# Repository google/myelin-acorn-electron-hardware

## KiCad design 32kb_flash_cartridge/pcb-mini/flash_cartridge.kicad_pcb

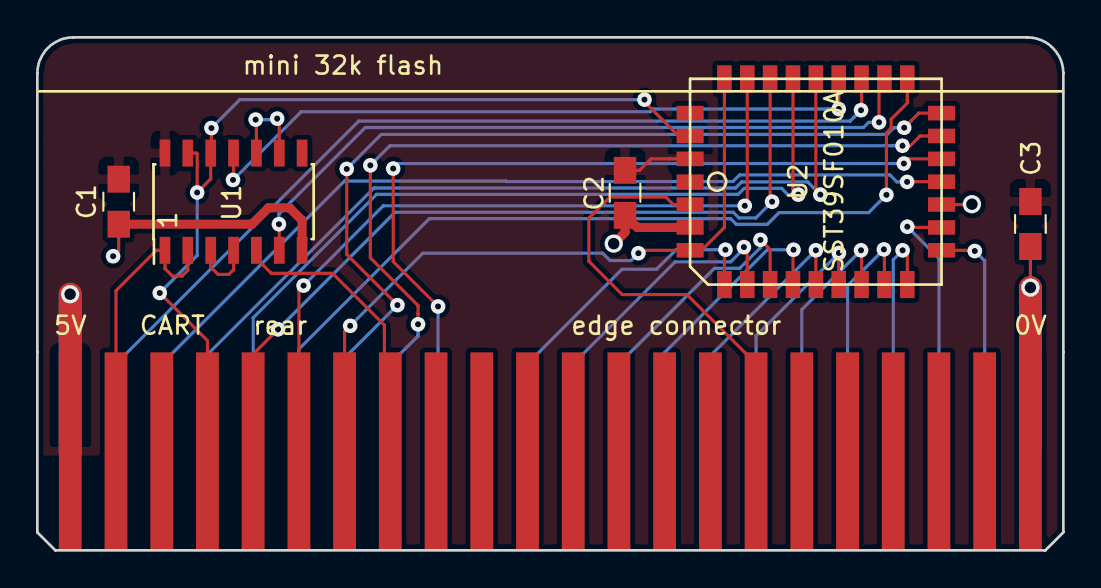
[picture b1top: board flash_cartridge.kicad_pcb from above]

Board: 2 copper layers, 57.0 x 28.5 mm, 6 parts (0 on the bottom side), 31 nets.

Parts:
C1, C2: 100n; C_0805_HandSoldering
C3: 10u; C_0805_HandSoldering
CART: edge connector; acorn_electron_cartridge_edge_connector
U1: 74HCT00; SOIC-14_3.9x8.7mm_Pitch1.27mm
U2: SST39SF010A; sst_plcc32_nh

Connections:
5V: C1.1, C2.1, C3.1, CART.A1, CART.B1, U1.14, U2.32
GND: C1.2, C2.2, C3.2, CART.A22, CART.B22, U1.7, U1.9, U1.10, U2.3, U2.16
elk_A0: CART.B18, U2.12
elk_A1: CART.B17, U2.11
elk_A2: CART.B16, U2.10
elk_A3: CART.B15, U2.9
elk_A4: CART.B14, U2.8
elk_A5: CART.B13, U2.7
elk_A6: CART.B12, U2.6
elk_A7: CART.B11, U2.5
elk_A8: CART.A5, U2.27
elk_A9: CART.B5, U2.26
elk_A10: CART.B2, U2.23
elk_A11: CART.B4, U2.25
elk_A12: CART.A7, U2.4, U2.29
elk_A13: CART.A6, U2.28
elk_D0: CART.B19, U2.13
elk_D1: CART.B21, U2.14
elk_D2: CART.B20, U2.15
elk_D3: CART.B3, U2.17
elk_D4: CART.B9, U2.18
elk_D5: CART.B8, U2.19
elk_D6: CART.B7, U2.20
elk_D7: CART.B6, U2.21
elk_PHI0: CART.A8, U1.5
elk_ROMQA: CART.A16, U2.2
elk_RnW: CART.A4, U1.12, U1.13, U2.31
elk_nOE: CART.A2, U1.1, U1.2
flash_nCE: U1.6, U2.22
flash_nOE: U1.11, U2.24
not_elk_nOE: U1.3, U1.4

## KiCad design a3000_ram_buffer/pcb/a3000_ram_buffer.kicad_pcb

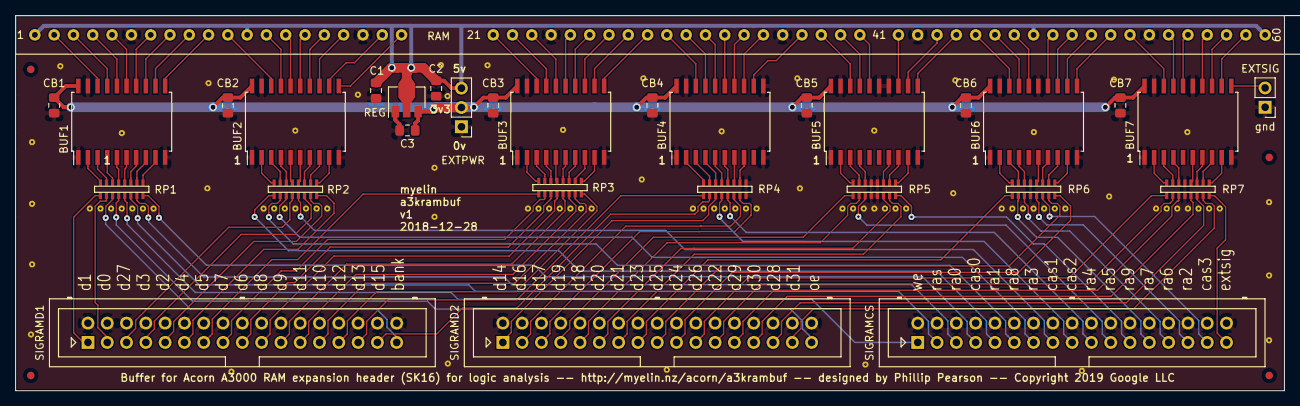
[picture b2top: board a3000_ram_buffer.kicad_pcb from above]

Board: 2 copper layers, 167.0 x 49.4 mm, 78 parts (0 on the bottom side), 156 nets.

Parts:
BUF1, BUF2, BUF3, BUF4, BUF5, BUF6, BUF7: 74LVC245; SOIC-20W_7.5x12.8mm_P1.27mm
C1: 10u; C_0805_2012Metric_Pad1.15x1.40mm_HandSolder
C2, C3: 1u; C_0805_2012Metric_Pad1.15x1.40mm_HandSolder
CB1, CB2, CB3, CB4, CB5, CB6, CB7: 100n; C_0805_2012Metric_Pad1.15x1.40mm_HandSolder
EXTPWR: ext pwr; PinHeader_1x03_P2.54mm_Vertical
EXTSIG: ext signal; PinHeader_1x02_P2.54mm_Vertical
FID1, FID2, FID3, FID4: FIDUCIAL; Fiducial_1mm_Dia_2mm_Outer
RAM: Extension socket to connect to RAM header on A300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; a3000_ram_header
REG: MCP1700T-3302E/MB; SOT-89-3
RP1, RP2, RP3, RP4, RP5, RP6, RP7: resistor pack; bourns_cat16_j8_resistor_array
SIGRAMCS: signal header RAMCS; Multicomp_MC9A12-3434_2x17_P2.54mm_Vertical
SIGRAMD1: signal header RAMD1; Multicomp_MC9A12-3434_2x17_P2.54mm_Vertical
SIGRAMD2: signal header RAMD2; Multicomp_MC9A12-3434_2x17_P2.54mm_Vertical
STAPLE1, STAPLE2, STAPLE3, STAPLE4, STAPLE5, STAPLE6, STAPLE7: via array; via_array_1x7_55mil
staple_single1, staple_single2, staple_single3, staple_single4, staple_single5, staple_single6, staple_single7, staple_single8, staple_single9, staple_single10, staple_single11, staple_single12, staple_single13, staple_single14, staple_single15, staple_single16, staple_single17, staple_single18, staple_single19, staple_single20, staple_single21, staple_single22, staple_single23, staple_single24, staple_single25, staple_single26, staple_single27, staple_single28, staple_single29, staple_single30, staple_single31, staple_single32, staple_single33, staple_single34, staple_single35, staple_single36: via_single

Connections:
3V3: BUF1.20, BUF2.20, BUF3.20, BUF4.20, BUF5.20, BUF6.20, BUF7.20, C3.1, CB1.2, CB2.2, CB3.2, CB4.2, CB5.2, CB6.2, CB7.2, EXTPWR.2, REG.3
5V: C1.2, C2.2, EXTPWR.3, RAM.1, RAM.12, RAM.48, RAM.60, REG.2
GND: BUF1.1, BUF1.10, BUF1.19, BUF2.1, BUF2.10, BUF2.19, BUF3.1, BUF3.10, BUF3.19, BUF4.1, BUF4.10, BUF4.11, BUF4.19, BUF5.1, BUF5.10, BUF5.14, BUF5.15, BUF5.19, BUF6.1, BUF6.10, BUF6.15, BUF6.19, BUF7.1, BUF7.10, BUF7.15, BUF7.19, C1.1, C2.1, C3.2, CB1.1, CB2.1, CB3.1, CB4.1, CB5.1, CB6.1, CB7.1, EXTPWR.1, EXTSIG.1, RAM.6, RAM.18, RAM.24, RAM.36, RAM.42, RAM.54, REG.1, RP4.8A, RP4.8B, RP5.4A, RP5.4B, RP5.5A, RP5.5B, RP6.4A, RP6.4B, RP7.4A, RP7.4B, SIGRAMCS.2, SIGRAMCS.4, SIGRAMCS.6, SIGRAMCS.8, SIGRAMCS.10, SIGRAMCS.12, SIGRAMCS.14, SIGRAMCS.16, SIGRAMCS.18, SIGRAMCS.20, SIGRAMCS.22, SIGRAMCS.24, SIGRAMCS.26, SIGRAMCS.28, SIGRAMCS.30, SIGRAMCS.32, SIGRAMCS.34, SIGRAMD1.2, SIGRAMD1.4, SIGRAMD1.6, SIGRAMD1.8, SIGRAMD1.10, SIGRAMD1.12, SIGRAMD1.14, SIGRAMD1.16, SIGRAMD1.18, SIGRAMD1.20, SIGRAMD1.22, SIGRAMD1.24, SIGRAMD1.26, SIGRAMD1.28, SIGRAMD1.30, SIGRAMD1.32, SIGRAMD1.34, SIGRAMD2.2, SIGRAMD2.4, SIGRAMD2.6, SIGRAMD2.8, SIGRAMD2.10, SIGRAMD2.12, SIGRAMD2.14, SIGRAMD2.16, SIGRAMD2.18, SIGRAMD2.20, SIGRAMD2.22, SIGRAMD2.24, SIGRAMD2.26, SIGRAMD2.28, SIGRAMD2.30, SIGRAMD2.32, SIGRAMD2.34, STAPLE1.1, STAPLE1.2, STAPLE1.3, STAPLE1.4, STAPLE1.5, STAPLE1.6, STAPLE1.7, STAPLE2.1, STAPLE2.2, STAPLE2.3, STAPLE2.4, STAPLE2.5, STAPLE2.6, STAPLE2.7, STAPLE3.1, STAPLE3.2, STAPLE3.3, STAPLE3.4, STAPLE3.5, STAPLE3.6, STAPLE3.7, STAPLE4.1, STAPLE4.2, STAPLE4.3, STAPLE4.4, STAPLE4.5, STAPLE4.6, STAPLE4.7, STAPLE5.1, STAPLE5.2, STAPLE5.3, STAPLE5.4, STAPLE5.5, STAPLE5.6, STAPLE5.7, STAPLE6.1, STAPLE6.2, STAPLE6.3, STAPLE6.4, STAPLE6.5, STAPLE6.6, STAPLE6.7, STAPLE7.1, STAPLE7.2, STAPLE7.3, STAPLE7.4, STAPLE7.5, STAPLE7.6, STAPLE7.7, staple_single1.1, staple_single2.1, staple_single3.1, staple_single4.1, staple_single5.1, staple_single6.1, staple_single7.1, staple_single8.1, staple_single9.1, staple_single10.1, staple_single11.1, staple_single12.1, staple_single13.1, staple_single14.1, staple_single15.1, staple_single16.1, staple_single17.1, staple_single18.1, staple_single19.1, staple_single20.1, staple_single21.1, staple_single22.1, staple_single23.1, staple_single24.1, staple_single25.1, staple_single26.1, staple_single27.1, staple_single28.1, staple_single29.1, staple_single30.1, staple_single31.1, staple_single32.1, staple_single33.1, staple_single34.1, staple_single35.1, staple_single36.1
ext_signal: BUF7.11, EXTSIG.2
ext_signal_buf: BUF7.9, RP7.8B
ext_signal_term: RP7.8A, SIGRAMCS.33
ram_BANK: BUF1.16, RAM.4
ram_BANK_buf: BUF1.4, RP1.3B
ram_BANK_term: RP1.3A, SIGRAMD1.33
ram_D0: BUF1.17, RAM.3
ram_D0_buf: BUF1.3, RP1.2B
ram_D0_term: RP1.2A, SIGRAMD1.3
ram_D1: BUF1.18, RAM.2
ram_D1_buf: BUF1.2, RP1.1B
ram_D1_term: RP1.1A, SIGRAMD1.1
ram_D2: BUF2.12, RAM.19
ram_D2_buf: BUF2.8, RP2.7B
ram_D2_term: RP2.7A, SIGRAMD1.9
ram_D3: BUF2.13, RAM.17
ram_D3_buf: BUF2.7, RP2.6B
ram_D3_term: RP2.6A, SIGRAMD1.7
ram_D4: BUF2.11, RAM.20
ram_D4_buf: BUF2.9, RP2.8B
ram_D4_term: RP2.8A, SIGRAMD1.11
ram_D5: BUF3.18, RAM.21
ram_D5_buf: BUF3.2, RP3.1B
ram_D5_term: RP3.1A, SIGRAMD1.13
ram_D6: BUF3.16, RAM.23
ram_D6_buf: BUF3.4, RP3.3B
ram_D6_term: RP3.3A, SIGRAMD1.17
ram_D7: BUF3.17, RAM.22
ram_D7_buf: BUF3.3, RP3.2B
ram_D7_term: RP3.2A, SIGRAMD1.15
ram_D8: BUF3.15, RAM.25
ram_D8_buf: BUF3.5, RP3.4B
ram_D8_term: RP3.4A, SIGRAMD1.19
ram_D9: BUF3.14, RAM.26
ram_D9_buf: BUF3.6, RP3.5B
ram_D9_term: RP3.5A, SIGRAMD1.21
ram_D10: BUF3.12, RAM.28
ram_D10_buf: BUF3.8, RP3.7B
ram_D10_term: RP3.7A, SIGRAMD1.25
ram_D11: BUF3.13, RAM.27
ram_D11_buf: BUF3.7, RP3.6B
ram_D11_term: RP3.6A, SIGRAMD1.23
ram_D12: BUF3.11, RAM.29
ram_D12_buf: BUF3.9, RP3.8B
ram_D12_term: RP3.8A, SIGRAMD1.27
ram_D13: BUF4.18, RAM.30
ram_D13_buf: BUF4.2, RP4.1B
ram_D13_term: RP4.1A, SIGRAMD1.29
ram_D14: BUF4.16, RAM.32
ram_D14_buf: BUF4.4, RP4.3B
ram_D14_term: RP4.3A, SIGRAMD2.1
ram_D15: BUF4.17, RAM.31
ram_D15_buf: BUF4.3, RP4.2B
ram_D15_term: RP4.2A, SIGRAMD1.31
ram_D16: BUF4.13, RAM.35
ram_D16_buf: BUF4.7, RP4.6B
ram_D16_term: RP4.6A, SIGRAMD2.3
ram_D17: BUF4.12, RAM.37
ram_D17_buf: BUF4.8, RP4.7B
ram_D17_term: RP4.7A, SIGRAMD2.5
ram_D18: BUF5.17, RAM.39
ram_D18_buf: BUF5.3, RP5.2B
ram_D18_term: RP5.2A, SIGRAMD2.9
ram_D19: BUF5.18, RAM.38
ram_D19_buf: BUF5.2, RP5.1B
ram_D19_term: RP5.1A, SIGRAMD2.7
ram_D20: BUF5.13, RAM.41
ram_D20_buf: BUF5.7, RP5.6B
ram_D20_term: RP5.6A, SIGRAMD2.11
ram_D21: BUF5.12, RAM.43
ram_D21_buf: BUF5.8, RP5.7B
ram_D21_term: RP5.7A, SIGRAMD2.13
ram_D22: BUF7.17, RAM.55
ram_D22_buf: BUF7.3, RP7.2B
ram_D22_term: RP7.2A, SIGRAMD2.23
ram_D23: BUF6.18, RAM.45
ram_D23_buf: BUF6.2, RP6.1B
ram_D23_term: RP6.1A, SIGRAMD2.15
ram_D24: BUF6.11, RAM.52
ram_D24_buf: BUF6.9, RP6.8B
ram_D24_term: RP6.8A, SIGRAMD2.19
ram_D25: BUF6.12, RAM.51
ram_D25_buf: BUF6.8, RP6.7B
ram_D25_term: RP6.7A, SIGRAMD2.17
ram_D26: BUF7.18, RAM.53
ram_D26_buf: BUF7.2, RP7.1B
ram_D26_term: RP7.1A, SIGRAMD2.21
ram_D27: BUF2.15, RAM.15
ram_D27_buf: BUF2.5, RP2.4B
ram_D27_term: RP2.4A, SIGRAMD1.5
ram_D28: BUF7.13, RAM.58
ram_D28_buf: BUF7.7, RP7.6B
ram_D28_term: RP7.6A, SIGRAMD2.29
ram_D29: BUF7.16, RAM.56
ram_D29_buf: BUF7.4, RP7.3B
ram_D29_term: RP7.3A, SIGRAMD2.25
ram_D30: BUF7.14, RAM.57
ram_D30_buf: BUF7.6, RP7.5B
ram_D30_term: RP7.5A, SIGRAMD2.27
ram_D31: BUF7.12, RAM.59
ram_D31_buf: BUF7.8, RP7.7B
ram_D31_term: RP7.7A, SIGRAMD2.31
ram_RA0: BUF1.12, RAM.9
ram_RA0_buf: BUF1.8, RP1.7B
ram_RA0_term: RP1.7A, SIGRAMCS.5
ram_RA1: BUF2.18, RAM.11
ram_RA1_buf: BUF2.2, RP2.1B
ram_RA1_term: RP2.1A, SIGRAMCS.9
ram_RA2: BUF6.14, RAM.49
ram_RA2_buf: BUF6.6, RP6.5B
ram_RA2_term: RP6.5A, SIGRAMCS.29
ram_RA3: BUF2.16, RAM.14
ram_RA3_buf: BUF2.4, RP2.3B
ram_RA3_term: RP2.3A, SIGRAMCS.13
ram_RA4: BUF4.14, RAM.34
ram_RA4_buf: BUF4.6, RP4.5B
ram_RA4_term: RP4.5A, SIGRAMCS.19
ram_RA5: BUF5.16, RAM.40
ram_RA5_buf: BUF5.4, RP5.3B
ram_RA5_term: RP5.3A, SIGRAMCS.21
ram_RA6: BUF6.16, RAM.47
ram_RA6_buf: BUF6.4, RP6.3B
ram_RA6_term: RP6.3A, SIGRAMCS.27
ram_RA7: BUF6.17, RAM.46
ram_RA7_buf: BUF6.3, RP6.2B
ram_RA7_term: RP6.2A, SIGRAMCS.25
ram_RA8: BUF2.17, RAM.13
ram_RA8_buf: BUF2.3, RP2.2B
ram_RA8_term: RP2.2A, SIGRAMCS.11
ram_RA9: BUF5.11, RAM.44
ram_RA9_buf: BUF5.9, RP5.8B
ram_RA9_term: RP5.8A, SIGRAMCS.23
ram_nCAS0: BUF1.11, RAM.10
ram_nCAS0_buf: BUF1.9, RP1.8B
ram_nCAS0_term: RP1.8A, SIGRAMCS.7
ram_nCAS1: BUF2.14, RAM.16
ram_nCAS1_buf: BUF2.6, RP2.5B
ram_nCAS1_term: RP2.5A, SIGRAMCS.15
ram_nCAS2: BUF4.15, RAM.33
ram_nCAS2_buf: BUF4.5, RP4.4B
ram_nCAS2_term: RP4.4A, SIGRAMCS.17
ram_nCAS3: BUF6.13, RAM.50
ram_nCAS3_buf: BUF6.7, RP6.6B
ram_nCAS3_term: RP6.6A, SIGRAMCS.31
ram_nOE2: BUF1.15, RAM.5
ram_nOE2_buf: BUF1.5, RP1.4B
ram_nOE2_term: RP1.4A, SIGRAMD2.33
ram_nRAS: BUF1.13, RAM.8
ram_nRAS_buf: BUF1.7, RP1.6B
ram_nRAS_term: RP1.6A, SIGRAMCS.3
ram_nWR2: BUF1.14, RAM.7
ram_nWR2_buf: BUF1.6, RP1.5B
ram_nWR2_term: RP1.5A, SIGRAMCS.1

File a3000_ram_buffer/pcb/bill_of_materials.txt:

Identifier	Value	Description	KiCad package
BUF1	74LVC245		Package_SO:SOIC-20W_7.5x12.8mm_P1.27mm
BUF2	74LVC245		Package_SO:SOIC-20W_7.5x12.8mm_P1.27mm
BUF3	74LVC245		Package_SO:SOIC-20W_7.5x12.8mm_P1.27mm
BUF4	74LVC245		Package_SO:SOIC-20W_7.5x12.8mm_P1.27mm
BUF5	74LVC245		Package_SO:SOIC-20W_7.5x12.8mm_P1.27mm
BUF6	74LVC245		Package_SO:SOIC-20W_7.5x12.8mm_P1.27mm
BUF7	74LVC245		Package_SO:SOIC-20W_7.5x12.8mm_P1.27mm
C1	10u	10u capacitor in 0805 package	Capacitor_SMD:C_0805_2012Metric_Pad1.15x1.40mm_HandSolder
C2	1u	1u capacitor in 0805 package	Capacitor_SMD:C_0805_2012Metric_Pad1.15x1.40mm_HandSolder
C3	1u	1u capacitor in 0805 package	Capacitor_SMD:C_0805_2012Metric_Pad1.15x1.40mm_HandSolder
CB1	100n	100n capacitor in 0805 package	Capacitor_SMD:C_0805_2012Metric_Pad1.15x1.40mm_HandSolder
CB2	100n	100n capacitor in 0805 package	Capacitor_SMD:C_0805_2012Metric_Pad1.15x1.40mm_HandSolder
CB3	100n	100n capacitor in 0805 package	Capacitor_SMD:C_0805_2012Metric_Pad1.15x1.40mm_HandSolder
CB4	100n	100n capacitor in 0805 package	Capacitor_SMD:C_0805_2012Metric_Pad1.15x1.40mm_HandSolder
CB5	100n	100n capacitor in 0805 package	Capacitor_SMD:C_0805_2012Metric_Pad1.15x1.40mm_HandSolder
CB6	100n	100n capacitor in 0805 package	Capacitor_SMD:C_0805_2012Metric_Pad1.15x1.40mm_HandSolder
CB7	100n	100n capacitor in 0805 package	Capacitor_SMD:C_0805_2012Metric_Pad1.15x1.40mm_HandSolder
EXTPWR	ext pwr	1x3 0.1 inch male header	Connector_PinHeader_2.54mm:PinHeader_1x03_P2.54mm_Vertical
EXTSIG	ext signal	1x2 0.1 inch male header	Connector_PinHeader_2.54mm:PinHeader_1x02_P2.54mm_Vertical
FID1	FIDUCIAL		Fiducial:Fiducial_1mm_Dia_2mm_Outer
FID2	FIDUCIAL		Fiducial:Fiducial_1mm_Dia_2mm_Outer
FID3	FIDUCIAL		Fiducial:Fiducial_1mm_Dia_2mm_Outer
FID4	FIDUCIAL		Fiducial:Fiducial_1mm_Dia_2mm_Outer
RAM	Extension socket to connect to RAM header on A3000 motherboard, and mezzanine RAM board		myelin-kicad:a3000_ram_header
REG	MCP1700T-3302E/MB	3.3V LDO regulator, e.g. Digikey MCP1700T3302EMBCT-ND.  Search for the exact part number because there are many variants.	Package_TO_SOT_SMD:SOT-89-3
RP1	resistor pack	8 x 68R	myelin-kicad:bourns_cat16_j8_resistor_array
RP2	resistor pack	8 x 68R	myelin-kicad:bourns_cat16_j8_resistor_array
RP3	resistor pack	8 x 68R	myelin-kicad:bourns_cat16_j8_resistor_array
RP4	resistor pack	8 x 68R	myelin-kicad:bourns_cat16_j8_resistor_array
RP5	resistor pack	8 x 68R	myelin-kicad:bourns_cat16_j8_resistor_array
RP6	resistor pack	8 x 68R	myelin-kicad:bourns_cat16_j8_resistor_array
RP7	resistor pack	8 x 68R	myelin-kicad:bourns_cat16_j8_resistor_array
SIGRAMCS	signal header RAMCS	2x17 0.1 inch male header	Connector_Multicomp:Multicomp_MC9A12-3434_2x17_P2.54mm_Vertical
SIGRAMD1	signal header RAMD1	2x17 0.1 inch male header	Connector_Multicomp:Multicomp_MC9A12-3434_2x17_P2.54mm_Vertical
SIGRAMD2	signal header RAMD2	2x17 0.1 inch male header	Connector_Multicomp:Multicomp_MC9A12-3434_2x17_P2.54mm_Vertical
STAPLE1	via array		myelin-kicad:via_array_1x7_55mil
STAPLE2	via array		myelin-kicad:via_array_1x7_55mil
STAPLE3	via array		myelin-kicad:via_array_1x7_55mil
STAPLE4	via array		myelin-kicad:via_array_1x7_55mil
STAPLE5	via array		myelin-kicad:via_array_1x7_55mil
STAPLE6	via array		myelin-kicad:via_array_1x7_55mil
STAPLE7	via array		myelin-kicad:via_array_1x7_55mil

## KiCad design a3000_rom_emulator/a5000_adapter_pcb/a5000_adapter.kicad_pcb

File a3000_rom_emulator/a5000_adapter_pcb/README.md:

Adapter board to allow an "arcflash" A3000 ROM emulator to work on an A5000.

Pictures
--------

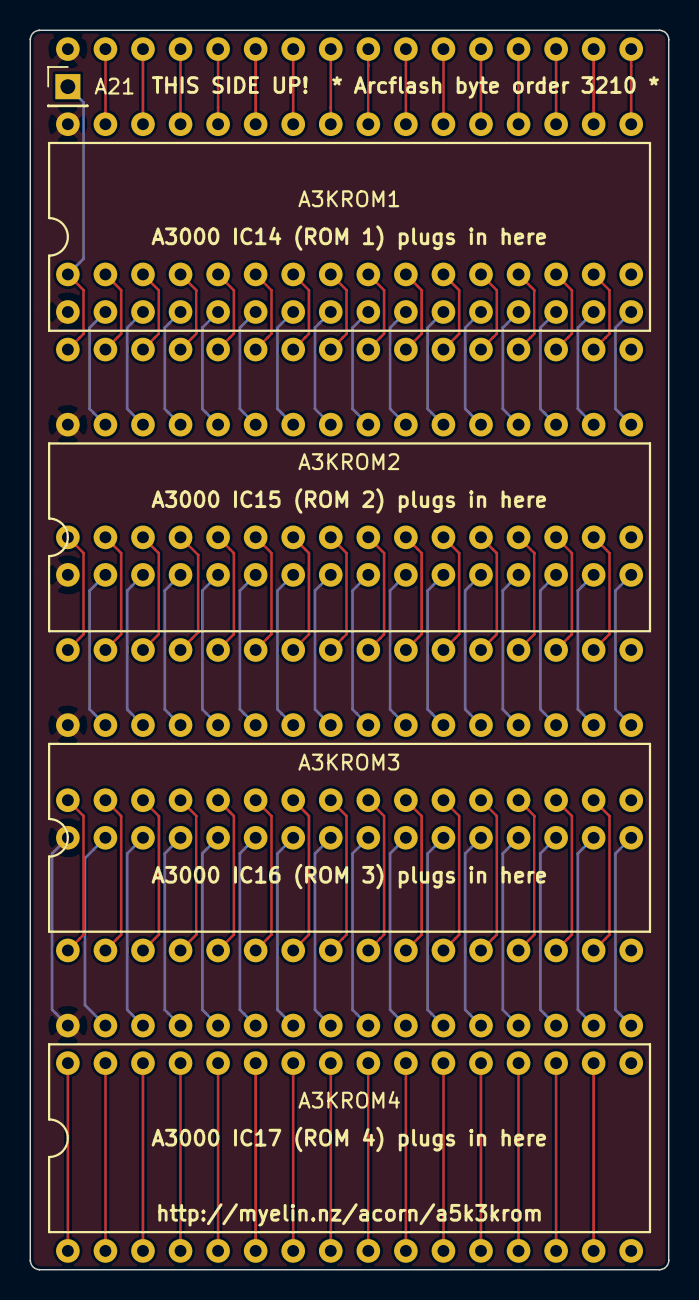
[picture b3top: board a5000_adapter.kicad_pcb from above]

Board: 2 copper layers, 43.2 x 83.8 mm, 9 parts (0 on the bottom side), 122 nets.

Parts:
A3KROM1, A3KROM2, A3KROM3, A3KROM4: ROM header; dip32_rom
A5KROM1, A5KROM2, A5KROM3, A5KROM4: ROM header; dip32_rom_bottom
A21: PinHeader_1x01_P2.54mm_Vertical

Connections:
GND: A3KROM1.16, A3KROM2.16, A3KROM3.16, A3KROM4.16, A5KROM1.16, A5KROM2.16, A5KROM3.16, A5KROM4.16
rom1_pin1: A3KROM1.1, A5KROM1.1, A21.1
rom1_pin2: A3KROM1.2, A5KROM1.2
rom1_pin3: A3KROM1.3, A5KROM1.3
rom1_pin4: A3KROM1.4, A5KROM1.4
rom1_pin5: A3KROM1.5, A5KROM1.5
rom1_pin6: A3KROM1.6, A5KROM1.6
rom1_pin7: A3KROM1.7, A5KROM1.7
rom1_pin8: A3KROM1.8, A5KROM1.8
rom1_pin9: A3KROM1.9, A5KROM1.9
rom1_pin10: A3KROM1.10, A5KROM1.10
rom1_pin11: A3KROM1.11, A5KROM1.11
rom1_pin12: A3KROM1.12, A5KROM1.12
rom1_pin13: A3KROM1.13, A5KROM1.13
rom1_pin14: A3KROM1.14, A5KROM1.14
rom1_pin15: A3KROM1.15, A5KROM1.15
rom1_pin17: A3KROM1.17, A5KROM1.17
rom1_pin18: A3KROM1.18, A5KROM1.18
rom1_pin19: A3KROM1.19, A5KROM1.19
rom1_pin20: A3KROM1.20, A5KROM1.20
rom1_pin21: A3KROM1.21, A5KROM1.21
rom1_pin22: A3KROM1.22, A5KROM1.22
rom1_pin23: A3KROM1.23, A5KROM1.23
rom1_pin24: A3KROM1.24, A5KROM1.24
rom1_pin25: A3KROM1.25, A5KROM1.25
rom1_pin26: A3KROM1.26, A5KROM1.26
rom1_pin27: A3KROM1.27, A5KROM1.27
rom1_pin28: A3KROM1.28, A5KROM1.28
rom1_pin29: A3KROM1.29, A5KROM1.29
rom1_pin30: A3KROM1.30, A5KROM1.30
rom1_pin31: A3KROM1.31, A5KROM1.31
rom2_pin1: A3KROM2.1, A5KROM2.1
rom2_pin2: A3KROM2.2, A5KROM2.2
rom2_pin3: A3KROM2.3, A5KROM2.3
rom2_pin4: A3KROM2.4, A5KROM2.4
rom2_pin5: A3KROM2.5, A5KROM2.5
rom2_pin6: A3KROM2.6, A5KROM2.6
rom2_pin7: A3KROM2.7, A5KROM2.7
rom2_pin8: A3KROM2.8, A5KROM2.8
rom2_pin9: A3KROM2.9, A5KROM2.9
rom2_pin10: A3KROM2.10, A5KROM2.10
rom2_pin11: A3KROM2.11, A5KROM2.11
rom2_pin12: A3KROM2.12, A5KROM2.12
rom2_pin13: A3KROM2.13, A5KROM2.13
rom2_pin14: A3KROM2.14, A5KROM2.14
rom2_pin15: A3KROM2.15, A5KROM2.15
rom2_pin17: A3KROM2.17, A5KROM2.17
rom2_pin18: A3KROM2.18, A5KROM2.18
rom2_pin19: A3KROM2.19, A5KROM2.19
rom2_pin20: A3KROM2.20, A5KROM2.20
rom2_pin21: A3KROM2.21, A5KROM2.21
rom2_pin22: A3KROM2.22, A5KROM2.22
rom2_pin23: A3KROM2.23, A5KROM2.23
rom2_pin24: A3KROM2.24, A5KROM2.24
rom2_pin25: A3KROM2.25, A5KROM2.25
rom2_pin26: A3KROM2.26, A5KROM2.26
rom2_pin27: A3KROM2.27, A5KROM2.27
rom2_pin28: A3KROM2.28, A5KROM2.28
rom2_pin29: A3KROM2.29, A5KROM2.29
rom2_pin30: A3KROM2.30, A5KROM2.30
rom2_pin31: A3KROM2.31, A5KROM2.31
rom3_pin1: A3KROM3.1, A5KROM3.1
rom3_pin2: A3KROM3.2, A5KROM3.2
rom3_pin3: A3KROM3.3, A5KROM3.3
rom3_pin4: A3KROM3.4, A5KROM3.4
rom3_pin5: A3KROM3.5, A5KROM3.5
rom3_pin6: A3KROM3.6, A5KROM3.6
rom3_pin7: A3KROM3.7, A5KROM3.7
rom3_pin8: A3KROM3.8, A5KROM3.8
rom3_pin9: A3KROM3.9, A5KROM3.9
rom3_pin10: A3KROM3.10, A5KROM3.10
rom3_pin11: A3KROM3.11, A5KROM3.11
rom3_pin12: A3KROM3.12, A5KROM3.12
rom3_pin13: A3KROM3.13, A5KROM3.13
rom3_pin14: A3KROM3.14, A5KROM3.14
rom3_pin15: A3KROM3.15, A5KROM3.15
rom3_pin17: A3KROM3.17, A5KROM3.17
rom3_pin18: A3KROM3.18, A5KROM3.18
rom3_pin19: A3KROM3.19, A5KROM3.19
rom3_pin20: A3KROM3.20, A5KROM3.20
rom3_pin21: A3KROM3.21, A5KROM3.21
rom3_pin22: A3KROM3.22, A5KROM3.22
rom3_pin23: A3KROM3.23, A5KROM3.23
rom3_pin24: A3KROM3.24, A5KROM3.24
rom3_pin25: A3KROM3.25, A5KROM3.25
rom3_pin26: A3KROM3.26, A5KROM3.26
rom3_pin27: A3KROM3.27, A5KROM3.27
rom3_pin28: A3KROM3.28, A5KROM3.28
rom3_pin29: A3KROM3.29, A5KROM3.29
rom3_pin30: A3KROM3.30, A5KROM3.30
rom3_pin31: A3KROM3.31, A5KROM3.31
rom4_pin1: A3KROM4.1, A5KROM4.1
rom4_pin2: A3KROM4.2, A5KROM4.2
rom4_pin3: A3KROM4.3, A5KROM4.3
rom4_pin4: A3KROM4.4, A5KROM4.4
rom4_pin5: A3KROM4.5, A5KROM4.5
rom4_pin6: A3KROM4.6, A5KROM4.6
rom4_pin7: A3KROM4.7, A5KROM4.7
rom4_pin8: A3KROM4.8, A5KROM4.8
rom4_pin9: A3KROM4.9, A5KROM4.9
rom4_pin10: A3KROM4.10, A5KROM4.10
rom4_pin11: A3KROM4.11, A5KROM4.11
rom4_pin12: A3KROM4.12, A5KROM4.12
rom4_pin13: A3KROM4.13, A5KROM4.13
rom4_pin14: A3KROM4.14, A5KROM4.14
rom4_pin15: A3KROM4.15, A5KROM4.15
rom4_pin17: A3KROM4.17, A5KROM4.17
rom4_pin18: A3KROM4.18, A5KROM4.18
rom4_pin19: A3KROM4.19, A5KROM4.19
rom4_pin20: A3KROM4.20, A5KROM4.20
rom4_pin21: A3KROM4.21, A5KROM4.21
rom4_pin22: A3KROM4.22, A5KROM4.22
rom4_pin23: A3KROM4.23, A5KROM4.23
rom4_pin24: A3KROM4.24, A5KROM4.24
rom4_pin25: A3KROM4.25, A5KROM4.25
rom4_pin26: A3KROM4.26, A5KROM4.26
rom4_pin27: A3KROM4.27, A5KROM4.27
rom4_pin28: A3KROM4.28, A5KROM4.28
rom4_pin29: A3KROM4.29, A5KROM4.29
rom4_pin30: A3KROM4.30, A5KROM4.30
rom4_pin31: A3KROM4.31, A5KROM4.31
rom_5V: A3KROM1.32, A3KROM2.32, A3KROM3.32, A3KROM4.32, A5KROM1.32, A5KROM2.32, A5KROM3.32, A5KROM4.32

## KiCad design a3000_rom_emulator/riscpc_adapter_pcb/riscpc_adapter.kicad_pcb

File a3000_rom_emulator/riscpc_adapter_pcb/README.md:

Adapter board to allow an "arcflash" A3000 ROM emulator to work on a Risc PC.

Pictures
--------

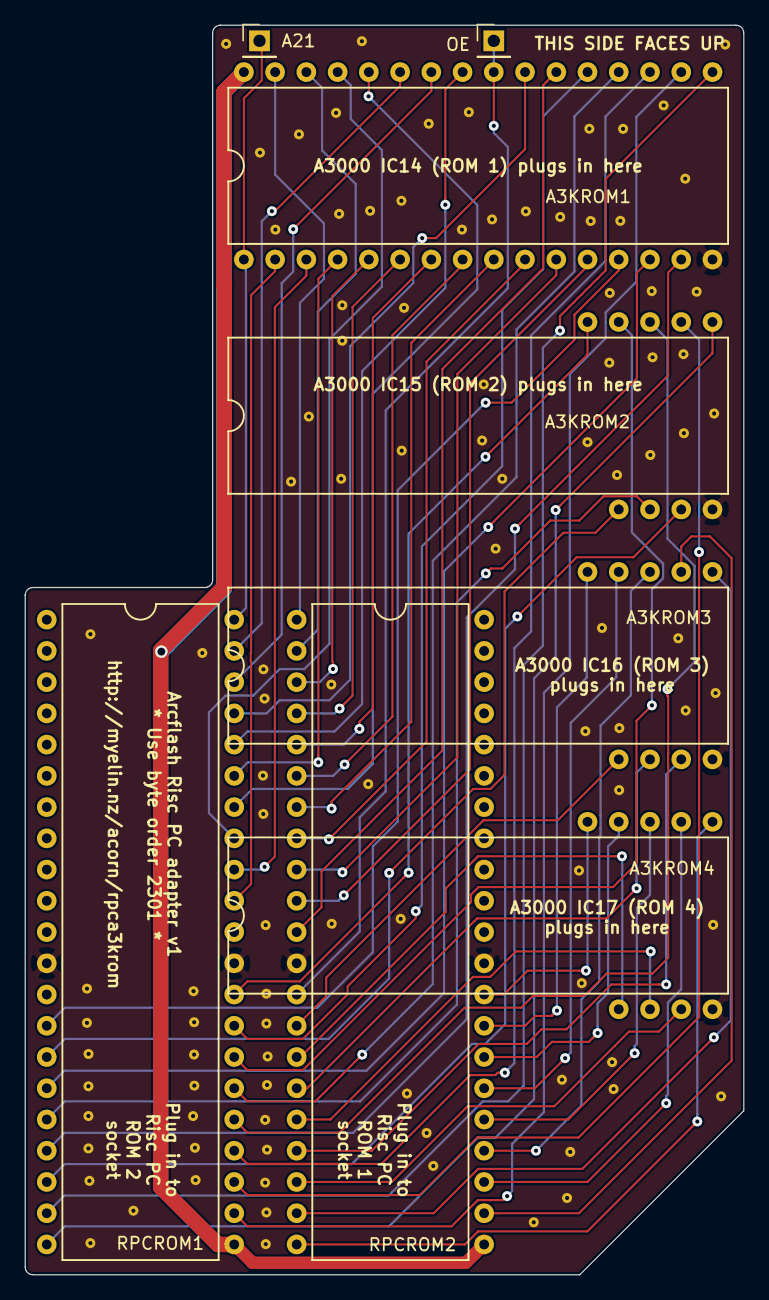
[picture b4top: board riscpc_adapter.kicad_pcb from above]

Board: 2 copper layers, 58.4 x 101.6 mm, 108 parts (0 on the bottom side), 56 nets.

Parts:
A3KROM1: ROM header; dip32_rom
A3KROM2, A3KROM3, A3KROM4: ROM header; dip32_rom_data_only
A21: PinHeader_1x01_P2.54mm_Vertical
OE: PinHeader_1x01_P2.54mm_Vertical
RPCROM1, RPCROM2: ROM header; dip42_rom
staple_single1, staple_single2, staple_single3, staple_single4, staple_single5, staple_single6, staple_single7, staple_single8, staple_single9, staple_single10, staple_single11, staple_single12, staple_single13, staple_single14, staple_single15, staple_single16, staple_single17, staple_single18, staple_single19, staple_single20, staple_single21, staple_single22, staple_single23, staple_single24, staple_single25, staple_single26, staple_single27, staple_single28, staple_single29, staple_single30, staple_single31, staple_single32, staple_single33, staple_single34, staple_single35, staple_single36, staple_single37, staple_single38, staple_single39, staple_single40, staple_single41, staple_single42, staple_single43, staple_single44, staple_single45, staple_single46, staple_single47, staple_single48, staple_single49, staple_single50, staple_single51, staple_single52, staple_single53, staple_single54, staple_single55, staple_single56, staple_single57, staple_single58, staple_single59, staple_single60, staple_single61, staple_single62, staple_single63, staple_single64, staple_single65, staple_single66, staple_single67, staple_single68, staple_single69, staple_single70, staple_single71, staple_single72, staple_single73, staple_single74, staple_single75, staple_single76, staple_single77, staple_single78, staple_single79, staple_single80, staple_single81, staple_single82, staple_single83, staple_single84, staple_single85, staple_single86, staple_single87, staple_single88, staple_single89, staple_single90, staple_single91, staple_single92, staple_single93, staple_single94, staple_single95, staple_single96, staple_single97, staple_single98, staple_single99, staple_single100: via_single

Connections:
5V: A3KROM1.32, RPCROM1.22, RPCROM2.22
A0: A3KROM1.12, RPCROM2.10
A1: A3KROM1.11, RPCROM2.9
A2: A3KROM1.10, RPCROM2.8
A3: A3KROM1.9, RPCROM2.7
A4: A3KROM1.8, RPCROM2.6
A5: A3KROM1.7, RPCROM2.5
A6: A3KROM1.6, RPCROM2.4
A7: A3KROM1.5, RPCROM2.3
A8: A3KROM1.27, RPCROM1.41
A9: A3KROM1.26, RPCROM1.40
A10: A3KROM1.23, RPCROM1.39
A11: A3KROM1.25, RPCROM1.38
A12: A3KROM1.4, RPCROM1.37
A13: A3KROM1.28, RPCROM1.36
A14: A3KROM1.29, RPCROM1.35
A15: A3KROM1.3, RPCROM1.34
A16: A3KROM1.2, RPCROM1.33
A17: A3KROM1.30, RPCROM2.2
A18: A3KROM1.31, RPCROM2.1
A19: A3KROM1.1, A21.1, RPCROM1.42
D0: A3KROM1.13, RPCROM1.14
D1: A3KROM1.14, RPCROM1.16
D2: A3KROM1.15, RPCROM1.18
D3: A3KROM1.17, RPCROM1.20
D4: A3KROM1.18, RPCROM1.23
D5: A3KROM1.19, RPCROM1.25
D6: A3KROM1.20, RPCROM1.27
D7: A3KROM1.21, RPCROM1.29
D8: A3KROM2.13, RPCROM1.15
D9: A3KROM2.14, RPCROM1.17
D10: A3KROM2.15, RPCROM1.19
D11: A3KROM2.17, RPCROM1.21
D12: A3KROM2.18, RPCROM1.24
D13: A3KROM2.19, RPCROM1.26
D14: A3KROM2.20, RPCROM1.28
D15: A3KROM2.21, RPCROM1.30
D16: A3KROM3.13, RPCROM2.14
D17: A3KROM3.14, RPCROM2.16
D18: A3KROM3.15, RPCROM2.18
D19: A3KROM3.17, RPCROM2.20
D20: A3KROM3.18, RPCROM2.23
D21: A3KROM3.19, RPCROM2.25
D22: A3KROM3.20, RPCROM2.27
D23: A3KROM3.21, RPCROM2.29
D24: A3KROM4.13, RPCROM2.15
D25: A3KROM4.14, RPCROM2.17
D26: A3KROM4.15, RPCROM2.19
D27: A3KROM4.17, RPCROM2.21
D28: A3KROM4.18, RPCROM2.24
D29: A3KROM4.19, RPCROM2.26
D30: A3KROM4.20, RPCROM2.28
D31: A3KROM4.21, RPCROM2.30
GND: A3KROM1.16, A3KROM2.16, A3KROM3.16, A3KROM4.16, RPCROM1.12, RPCROM1.31, RPCROM2.12, RPCROM2.31, staple_single1.1, staple_single2.1, staple_single3.1, staple_single4.1, staple_single5.1, staple_single6.1, staple_single7.1, staple_single8.1, staple_single9.1, staple_single10.1, staple_single11.1, staple_single12.1, staple_single13.1, staple_single14.1, staple_single15.1, staple_single16.1, staple_single17.1, staple_single18.1, staple_single19.1, staple_single20.1, staple_single21.1, staple_single22.1, staple_single23.1, staple_single24.1, staple_single25.1, staple_single26.1, staple_single27.1, staple_single28.1, staple_single29.1, staple_single30.1, staple_single31.1, staple_single32.1, staple_single33.1, staple_single34.1, staple_single35.1, staple_single36.1, staple_single37.1, staple_single38.1, staple_single39.1, staple_single40.1, staple_single41.1, staple_single42.1, staple_single43.1, staple_single44.1, staple_single45.1, staple_single46.1, staple_single47.1, staple_single48.1, staple_single49.1, staple_single50.1, staple_single51.1, staple_single52.1, staple_single53.1, staple_single54.1, staple_single55.1, staple_single56.1, staple_single57.1, staple_single58.1, staple_single59.1, staple_single60.1, staple_single61.1, staple_single62.1, staple_single63.1, staple_single64.1, staple_single65.1, staple_single66.1, staple_single67.1, staple_single68.1, staple_single69.1, staple_single70.1, staple_single71.1, staple_single72.1, staple_single73.1, staple_single74.1, staple_single75.1, staple_single76.1, staple_single77.1, staple_single78.1, staple_single79.1, staple_single80.1, staple_single81.1, staple_single82.1, staple_single83.1, staple_single84.1, staple_single85.1, staple_single86.1, staple_single87.1, staple_single88.1, staple_single89.1, staple_single90.1, staple_single91.1, staple_single92.1, staple_single93.1, staple_single94.1, staple_single95.1, staple_single96.1, staple_single97.1, staple_single98.1, staple_single99.1, staple_single100.1
nCS: A3KROM1.22, RPCROM2.11
nOE: A3KROM1.24, OE.1, RPCROM2.13

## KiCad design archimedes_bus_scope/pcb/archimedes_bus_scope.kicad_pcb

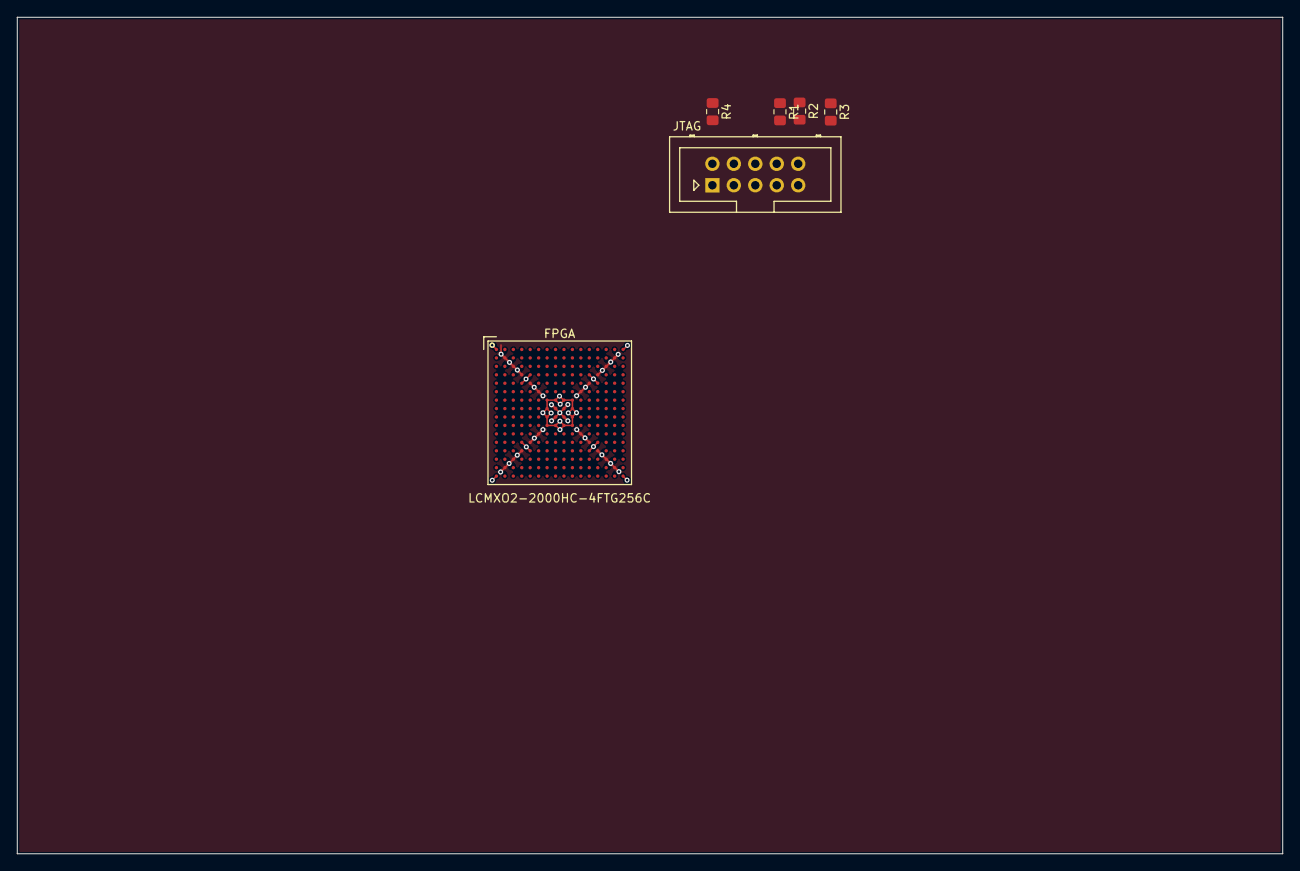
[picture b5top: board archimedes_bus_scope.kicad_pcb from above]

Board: 4 copper layers, 149.9 x 99.1 mm, 6 parts (0 on the bottom side), 9 nets.

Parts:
FPGA: LCMXO2-2000HC-4FTG256C; lattice_ftg256_fbga
JTAG: jtag; Multicomp_MC9A12-1034_2x05_P2.54mm_Vertical
R1, R2, R3: 10k; R_0805_2012Metric_Pad1.15x1.40mm_HandSolder
R4: 4k7; R_0805_2012Metric_Pad1.15x1.40mm_HandSolder

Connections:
3V3: FPGA.A1, FPGA.A16, FPGA.D5, FPGA.D12, FPGA.E4, FPGA.E13, FPGA.G7, FPGA.G8, FPGA.G9, FPGA.G10, FPGA.H7, FPGA.H10, FPGA.J7, FPGA.J10, FPGA.K7, FPGA.K8, FPGA.K9, FPGA.K10, FPGA.M4, FPGA.M13, FPGA.N5, FPGA.N12, FPGA.T1, FPGA.T16, JTAG.6, R1.1, R2.1, R3.1
GND: FPGA.B2, FPGA.B15, FPGA.C3, FPGA.C14, FPGA.D4, FPGA.D13, FPGA.E5, FPGA.E12, FPGA.F6, FPGA.F11, FPGA.H8, FPGA.H9, FPGA.J8, FPGA.J9, FPGA.L6, FPGA.L11, FPGA.M5, FPGA.M12, FPGA.N4, FPGA.N13, FPGA.P3, FPGA.P14, FPGA.R2, FPGA.R15, JTAG.2, JTAG.4, R4.1
fpga_DONE: FPGA.C13, JTAG.9, R3.2
fpga_INITN: FPGA.A13, JTAG.8, R1.2
fpga_PROGRAMN: FPGA.B10, JTAG.10, R2.2
fpga_TCK: FPGA.A7, JTAG.1, R4.2
fpga_TDI: FPGA.A6, JTAG.5
fpga_TDO: FPGA.C6, JTAG.7
fpga_TMS: FPGA.B8, JTAG.3

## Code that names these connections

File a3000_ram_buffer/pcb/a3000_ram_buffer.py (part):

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    pins=[
        # 32 data lines, 8 control lines (bank, oe, wr, ras, 4xcas), four 5V, six GND, 10 address = 60 pins
        Pin( 1, "5V",    "5V"),
        Pin( 2, "Rd1",   "ram_D1"),
        Pin( 3, "Rd0",   "ram_D0"),
        Pin( 4, "Bank",  "ram_BANK"),
        Pin( 5, "Oe2",   "ram_nOE2"),
        Pin( 6, "GND",   "GND"),
        Pin( 7, "Wr2",   "ram_nWR2"),
        Pin( 8, "Ras*",  "ram_nRAS"),
        Pin( 9, "Ra0",   "ram_RA0"),
        Pin(10, "Cas0*", "ram_nCAS0"),
        Pin(11, "Ra1",   "ram_RA1"),
        Pin(12, "5V",    "5V"),
        Pin(13, "Ra8",   "ram_RA8"),
        Pin(14, "Ra3",   "ram_RA3"),
        Pin(15, "Rd27",  "ram_D27"),
        Pin(16, "Cas1*", "ram_nCAS1"),
        Pin(17, "Rd3",   "ram_D3"),
        Pin(18, "GND",   "GND"),
        Pin(19, "Rd2",   "ram_D2"),
        Pin(20, "Rd4",   "ram_D4"),

        Pin(21, "Rd5",   "ram_D5"),
        Pin(22, "Rd7",   "ram_D7"),
        Pin(23, "Rd6",   "ram_D6"),
        Pin(24, "GND",   "GND"),
        Pin(25, "Rd8",   "ram_D8"),
        Pin(26, "Rd9",   "ram_D9"),
        Pin(27, "Rd11",  "ram_D11"),
        Pin(28, "Rd10",  "ram_D10"),
        Pin(29, "Rd12",  "ram_D12"),
        Pin(30, "Rd13",  "ram_D13"),
        Pin(31, "Rd15",  "ram_D15"),
        Pin(32, "Rd14",  "ram_D14"),
        Pin(33, "Cas2*", "ram_nCAS2"),
        Pin(34, "Ra4",   "ram_RA4"),
        Pin(35, "Rd16",  "ram_D16"),
        Pin(36, "GND",   "GND"),
        Pin(37, "Rd17",  "ram_D17"),
        Pin(38, "Rd19",  "ram_D19"),
        Pin(39, "Rd18",  "ram_D18"),
        Pin(40, "Ra5",   "ram_RA5"),
        
        Pin(41, "Rd20",  "ram_D20"),
        Pin(42, "GND",   "GND"),
        Pin(43, "Rd21",  "ram_D21"),
        Pin(44, "Ra9",   "ram_RA9"),
        Pin(45, "Rd23",  "ram_D23"),
        Pin(46, "Ra7",   "ram_RA7"),
        Pin(47, "Ra6",   "ram_RA6"),
        Pin(48, "5V",    "5V"),
        Pin(49, "Ra2",   "ram_RA2"),
        Pin(50, "Cas3*", "ram_nCAS3"),
        Pin(51, "Rd25",  "ram_D25"),
        Pin(52, "Rd24",  "ram_D24"),
        Pin(53, "Rd26",  "ram_D26"),
        Pin(54, "GND",   "GND"),
        Pin(55, "Rd22",  "ram_D22"),
        Pin(56, "Rd29",  "ram_D29"),
        Pin(57, "Rd30",  "ram_D30"),
        Pin(58, "Rd28",  "ram_D28"),
        Pin(59, "Rd31",  "ram_D31"),
        Pin(60, "5V",    "5V"),
    ],
)
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    desc="1x2 0.1 inch male header",
    pins=[
        Pin(1, "", "GND"),
        Pin(2, "", "ext_signal"),
    ],
)

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#             Pin(22, "2B6",  ""),
#             Pin(23, "2B7",  ""),
#             Pin(24, "2DIR", ""),
#             Pin(25, "2nOE", ""),
#             Pin(26, "2A7",  ""),
#             Pin(27, "2A6",  ""),
#             Pin(28, "GND",  "GND"),
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#             Pin(45, "GND",  "GND"),
#             Pin(46, "1A1",  ""),
#             Pin(47, "1A0",  ""),
#             Pin(48, "1nOE", ""),
#         ],
#     ),
# ]
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
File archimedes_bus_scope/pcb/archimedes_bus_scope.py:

#!/usr/bin/python

# Copyright 2018 Google LLC
#
# Licensed under the Apache License, Version 2.0 (the "License");
# you may not use this file except in compliance with the License.
# You may obtain a copy of the License at
#
#     http://www.apache.org/licenses/LICENSE-2.0
#
# Unless required by applicable law or agreed to in writing, software
# distributed under the License is distributed on an "AS IS" BASIS,
# WITHOUT WARRANTIES OR CONDITIONS OF ANY KIND, either express or implied.
# See the License for the specific language governing permissions and
# limitations under the License.

# --------------------
# archimedes_bus_scope
# --------------------

# by Phillip Pearson

# Interface board to allow sampling 128-ish logic channels over USB 3


PROJECT_NAME = "archimedes_bus_scope"


import sys, os
here = os.path.dirname(sys.argv[0])
sys.path.insert(0, os.path.join(here, "../../third_party/myelin-kicad.pretty"))
import myelin_kicad_pcb
Pin = myelin_kicad_pcb.Pin


"""
### FPGA connections: 207 IOs, and a bunch of VCC/GND/etc


### FX3 connections

# to FPGA: 32+12=44 pins
DQ0-31
PCLK # clock from FPGA
CTL0_SLCS# # select fx3
CTL1_SLWR# # write to fx3
CTL2_SLOE# # enable fx3 outputs
CTL3_SLRD# # read from fx3
CTL4_FLAGA
CTL5_FLAGB
CTL6_EPSWITCH
CTL7_PKTEND# # last byte of packet
CTL11_A1 # address
CTL12_A0 # address
CTL15_INT# # interrupt from fx3 to fpga

# to external?
GPIO45
GPIO53_RTS_SCK
GPIO54_CTS_SSN
GPIO55_TX_MISO
GPIO56_RX_MOSI

"""

# TODO think about footprint here.
# kicad's Package_BGA:BGA-256_17.0x17.0mm_Layout16x16_P1.0mm_Ball0.5mm_Pad0.4mm_NSMD
# has 0.4mm balls, which end up as 0.654mm with my 5 mil clearance, so have 0.346mm (13.6 mil)
# between them, i.e. plenty for two 4 mil traces and a 5 mil gap (13 mil).
# My myelin-kicad:cypress_lae064_fbga has 0.45mm balls, so 0.704 with clearance, and only 11.65 mil gap.

fpga = [
    myelin_kicad_pcb.Component(
        footprint="myelin-kicad:lattice_ftg256_fbga",
        identifier="FPGA",
        value="LCMXO2-2000HC-4FTG256C",
        buses=[""],
        pins=[
            # generated by make_machxo2_power_gnd_ball_map.py
            Pin("B2", "GND", "GND"),
            Pin("B15", "GND", "GND"),
            Pin("C3", "GND", "GND"),
            Pin("C14", "GND", "GND"),
            Pin("D4", "GND", "GND"),
            Pin("D13", "GND", "GND"),
            Pin("E5", "GND", "GND"),
            Pin("E12", "GND", "GND"),
            Pin("F6", "GND", "GND"),
            Pin("F11", "GND", "GND"),
            Pin("H8", "GND", "GND"),
            Pin("H9", "GND", "GND"),
            Pin("J8", "GND", "GND"),
            Pin("J9", "GND", "GND"),
            Pin("L6", "GND", "GND"),
            Pin("L11", "GND", "GND"),
            Pin("M5", "GND", "GND"),
            Pin("M12", "GND", "GND"),
            Pin("N4", "GND", "GND"),
            Pin("N13", "GND", "GND"),
            Pin("P3", "GND", "GND"),
            Pin("P14", "GND", "GND"),
            Pin("R2", "GND", "GND"),
            Pin("R15", "GND", "GND"),
            Pin("A1", "VCC", "3V3"),
            Pin("A16", "VCC", "3V3"),
            Pin("G7", "VCC", "3V3"),
            Pin("G10", "VCC", "3V3"),
            Pin("K7", "VCC", "3V3"),
            Pin("K10", "VCC", "3V3"),
            Pin("T1", "VCC", "3V3"),
            Pin("T16", "VCC", "3V3"),
            Pin("D5", "VCCIO0", "3V3"),
            Pin("D12", "VCCIO0", "3V3"),
            Pin("G8", "VCCIO0", "3V3"),
            Pin("G9", "VCCIO0", "3V3"),
            Pin("E13", "VCCIO1", "3V3"),
            Pin("H10", "VCCIO1", "3V3"),
            Pin("J10", "VCCIO1", "3V3"),
            Pin("M13", "VCCIO1", "3V3"),
            Pin("K8", "VCCIO2", "3V3"),
            Pin("K9", "VCCIO2", "3V3"),
            Pin("N5", "VCCIO2", "3V3"),
            Pin("N12", "VCCIO2", "3V3"),
            Pin("M4", "VCCIO3", "3V3"),
            Pin("H7", "VCCIO4", "3V3"),
            Pin("J7", "VCCIO4", "3V3"),
            Pin("E4", "VCCIO5", "3V3"),
            Pin("A2", "NC", "NC"),
        ] + [
            # Reserved during startup -- better leave NC or bring out to FX3
            Pin("A13", "INITN", "fpga_INITN"),
            Pin("B10", "PROGRAMN", "fpga_PROGRAMN"),
            Pin("C13", "DONE", "fpga_DONE"),

            # JTAG
            Pin("A6", "TDI", "fpga_TDI"),
            Pin("A7", "TCK", "fpga_TCK"),
            Pin("B8", "TMS", "fpga_TMS"),
            Pin("C6", "TDO", "fpga_TDO"),
        ] + [
            # User IO
        ],
    )
]

# MachXO2 needs a pullup on INITN to complete configuration, and pullups are also recommended on PROGRAMN and DONE.
# For JTAG, TMS, TDI, TDO have internal weak pullups, and TCK needs a 4k7 pulldown.
fpga_pullups = [
    myelin_kicad_pcb.R0805("10k", "3V3", "fpga_INITN"),
    myelin_kicad_pcb.R0805("10k", "3V3", "fpga_PROGRAMN"),
    myelin_kicad_pcb.R0805("10k", "3V3", "fpga_DONE"),
    myelin_kicad_pcb.R0805("4k7", "GND", "fpga_TCK"),
]

# TODO MachXO2 JTAG header, Lattice format
# See: https://github.com/google/myelin-acorn-electron-hardware/blob/master/notes/pld_programming_and_jtag.md
cpld_jtag = myelin_kicad_pcb.Component(
    footprint="Connector_Multicomp:Multicomp_MC9A12-1034_2x05_P2.54mm_Vertical",
    identifier="JTAG",
    value="jtag",
    desc="2x5 header for JTAG programming.  Use generic 0.1 inch header strip or Digikey ED1543-ND.",
    pins=[
        Pin( 1, "TCK",  "fpga_TCK"), # top left
        Pin( 2, "GND",  "GND"),      # top right
        Pin( 3, "TMS",  "fpga_TMS"),
        Pin( 4, "GND",  "GND"),
        Pin( 5, "TDI",  "fpga_TDI"),
        Pin( 6, "VCC",  "3V3"),
        Pin( 7, "TDO",  "fpga_TDO"),
        Pin( 8, "INIT", "fpga_INITN"),
        Pin( 9, "TRST", "fpga_DONE"),
        Pin(10, "PROG", "fpga_PROGRAMN"),
    ],
)
# I wasn't sure whether to put INIT on pin 8 or not -- uncomment this to make a test point for it
# cpld_INITN_TP = cpld_jtag = myelin_kicad_pcb.Component(
#     footprint="Connector_PinHeader_2.54mm:PinHeader_1x01_P2.54mm_Vertical",
#     identifier="INITN",
#     value="INITN test point",
#     desc="single header pin",
#     pins=[Pin(1, "INITN", "fpga_INITN")],
# )

myelin_kicad_pcb.dump_netlist("%s.net" % PROJECT_NAME)
myelin_kicad_pcb.dump_bom("bill_of_materials.txt",
                          "readable_bill_of_materials.txt")

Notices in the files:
a3000_ram_buffer/pcb/a3000_ram_buffer.py:
Copyright 2018 Google Inc.
32kb_flash_cartridge/pcb-mini/flash_cartridge.kicad_pcb:
Copyright (C) 2017 Google Inc
a3000_ram_buffer/pcb/a3000_ram_buffer.kicad_pcb:
Buffer for Acorn A3000 RAM expansion header (SK16) for logic analysis -- http://myelin.nz/acorn/a3krambuf -- designed by Phillip Pearson -- Copyright 2019 Google LLC
